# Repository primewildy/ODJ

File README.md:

# ODJ

A from-scratch DJ controller for Linux, written in Rust. Two decks, sub-3ms
output latency on PipeWire, MIDI controller support, in-app BPM + beat-grid
+ key detection, harmonic-mix filtering, and a phase vocoder for key-locked
tempo control.

Built as a side project; on the road to driving a custom microcontroller
hardware controller (RP2040 / ESP32-S3) speaking USB MIDI.

## Status

Working end-to-end as a two-deck mixing tool you can DJ a set on. Tested
with an AKAI LPD8 + homebrew **ODJ Controller** (`hardware/`) against a
library of ~550 mp3/flac tracks. The breadboard prototype of the
controller (Deck A: jog, transport buttons, 3-band EQ + volume + pitch
faders, Play LED) is fully working. A **two-deck carrier PCB**
(`hardware/pcb/`) is ready for fab — single Pico, JST-XH plug-in panel
connectors for all controls, plug-in CJMCU-4051 mux modules. A
**3D-printable faceplate** (`hardware/enclosure/`, parametric OpenSCAD)
matches it. Cue/PFL output works via a USB DAC dongle with PipeWire
routing handled automatically by `start-dj.sh`.

Built features:
- Two decks, cpal/PipeWire output at 256-frame buffers (~5.8 ms latency
  end-to-end; drops to ~2.9 ms at 128 if you run master only).
- Optional second cpal stream for **PFL / cue monitoring** on a separate
  output device (e.g. a USB DAC). **Headphone bus** with its own volume
  and a Pioneer-style **CUE↔MASTER blend** so you can mix the cued decks
  with the main mix in your headphones.
- Symphonia-based decode (mp3, flac, wav, aac/m4a).
- Phase-vocoder key-lock (with identity phase-locking for cleaner highs)
  + vinyl-style coupled-pitch mode per deck.
- 3-band EQ per deck (low 250 Hz shelf, mid 1 kHz bell, high 4 kHz shelf,
  ±25..+6 dB).
- Per-deck play-envelope (5 ms fade) — no click on transitions.
- BPM + beat-grid analysis (pure-Rust spectral flux + autocorr + brute
  force phase-aligned refinement, ~0.05 BPM precision).
- Downbeat detection via [beat_this](https://github.com/CPJKU/beat_this)
  exported to ONNX and run in-process from Rust via `ort` (CUDA EP).
  Red 4-bar lines on the beat grid; auto-snap of the playhead and cue
  point to the first downbeat on load. Optional — falls back to
  `i%4==0` if the ONNX file isn't present.
- **Live stem separation** via HTDemucs (
  [MansfieldPlumbing/Demucs_v4_TRT](https://huggingface.co/MansfieldPlumbing/Demucs_v4_TRT)
  ONNX) on the GPU through `ort` + TensorRT + FP16. ~7 s/track on an
  RTX 4060 Laptop. Three per-deck rotary knobs (DRUMS / VOCALS /
  INSTRUMENTS), 3-colour overlayed stem waveforms, in-memory
  session cache (not persisted to disk — too big). Tracks load and
  play immediately; the mixer transparently switches from the single
  buffer to the 4-stem mix when the worker finishes.
- Musical key detection (Krumhansl-Schmuckler) in Camelot notation.
- Auto Sync (BPM match) + auto Beat Align (phase-snap on play start
  *and* on every manual grid edit — so nudging a wonky grid against a
  known-good reference deck audibly converges step-by-step).
- Pioneer-style CUE state machine including the "Cue Play" commit.
- **Hot cues** — 8 slots per deck with the same set-vs-jump-vs-preview
  semantics as CUE. Jumps are beat-quantised when Q is on (defers
  the teleport to the next beat so sloppy press timing still lands
  cleanly). Right-click a slot to label it, pick a colour, or delete
  it. Persisted per-track to `.track-meta`. Coloured tick markers
  appear on both waveforms.
- **Manual beat-grid editing** — Grid Adjust tab in the source rail.
  Nudge ±1/±10 ms, skip ±1/2/4/8 beats, ½× / 2× BPM, set downbeat at
  playhead, reset. Locked by default each session so a stray click
  can't mangle a grid. Overrides persist to `.track-meta`; the manual
  grid wins over the analyser's refined output on every subsequent
  load.
- **Loops** — beat-quantised IN/OUT, one-shot 4-beat auto-loop, ½ /
  ×2 length, graceful Exit (plays out the current iteration), live
  "recording" highlight from IN to the playhead.
- **Per-deck FX** — beat-synced Echo (Type B, beat-picker UI) and
  Schroeder Reverb (Type A, continuous Time knob). Post-EQ, pre-fader
  so the cue bus tap is the wet signal.
- **Auto-mix** — armed state pre-loads a candidate next track on the
  idle deck; active blend ramps gains and drum-stem gates over the
  outgoing track's last 16 bars. Any deck-affecting user input
  cancels in-flight.
- Vinyl-style temporary push/pull nudge while held.
- Paused jog = audible scrub (forward + reverse). Click-to-seek on
  either waveform.
- Sortable track list (Title / Artist / Genre / Key / BPM / Length /
  Plays), favourites, harmonic compatibility filter, background
  analysis worker with disk persistence (and a `catch_unwind` around
  the DSP so a single pathological track can't kill the worker).
- **Session history** — every track played for ≥30 s is logged to
  `.history`. History tab groups by 2-hour gap into sessions;
  one-click setlist export to clipboard.
- **Settings UI** — audio/cue/MIDI device pickers, music-dir path,
  per-deck startup defaults. Persisted under XDG `~/.config/odj/`.
- **System theme** — light / dark follows the OS (gdbus + gsettings
  fallback); custom palette tokens for accents, stems and hot cues.
- LPD8 hardcoded mapping (pads + 8 knobs) with on-screen mirroring.
- **Homebrew hardware controller** prototype under `hardware/` — RP2040
  + optical encoder + arcade buttons + 74HC4051 analog mux. Class-
  compliant USB MIDI; sysex-triggered reboot for one-command re-flash
  (`hardware/flash.sh`). Two-deck carrier PCB (one Pico, both decks,
  JST-XH plug-in headers, CJMCU-4051 mux modules) generated from a
  SKiDL netlist (`hardware/pcb/odj_controller.py`) → KiCad → Gerbers.
  Parametric 3D-printed faceplate in `hardware/enclosure/`.

See [DESIGN.md](./DESIGN.md) for architecture and [TODO.md](./TODO.md) for
roadmap.

## Setup

Beyond `cargo` + the system audio stack, two of the bigger features need
out-of-band model files. The app runs fine without either — they're
gracefully optional — but you'll be missing red downbeat lines and stem
controls until they're in place.

All caches live under `~/.cache/dj/` (override with `$XDG_CACHE_HOME`).

### Models — runtime cache layout

| Path | What it is | Size | How to get it |
|---|---|---|---|
| `~/.cache/dj/model_final0.onnx` | beat_this downbeat model | ~85 MB | run [`scripts/export_beat_this_onnx.py`](./scripts/export_beat_this_onnx.py) in a Python venv that has `beat_this` installed, then `cp model_final0.onnx ~/.cache/dj/` |
| `~/.cache/dj/htdemucs.onnx` | HTDemucs stem-separation model | 246 MB | `curl -L -o ~/.cache/dj/htdemucs.onnx https://huggingface.co/MansfieldPlumbing/Demucs_v4_TRT/resolve/main/demucsv4.onnx` |
| `~/.cache/dj/trt-engines/` | TensorRT engine cache | ~190 MB after first build | created automatically on first stem separation (~15 min compile, cached after) |

Both files are runtime-loaded; nothing is bundled into the binary.

### TensorRT — for the fast stem path

The stems crate uses `ort`'s TensorRT execution provider. That needs
TensorRT 10.x libs (`libnvinfer.so.10`, `libnvinfer_plugin.so.10`,
`libnvonnxparser.so.10`) discoverable on `LD_LIBRARY_PATH`. The
easiest way: extract them from PyPI's `tensorrt-cu12-libs` wheel:

```sh
curl -L -o /tmp/trt.whl \
    https://pypi.nvidia.com/tensorrt-cu12-libs/tensorrt_cu12_libs-10.16.1.11-py3-none-manylinux_2_28_x86_64.whl
mkdir -p stem-spike/trt-libs && unzip -q /tmp/trt.whl -d stem-spike/trt-libs
```

`start-dj.sh` picks them up from `stem-spike/trt-libs/tensorrt_libs/`
automatically.

### CUDA — what ort needs at runtime

`ort` ships against CUDA 12 but ships a CUDA EP that's flexible.
On Arch with system CUDA 13.2 you can either:
- Install CUDA 12 alongside (e.g. via the matching `cuda-12.x` AUR
  package), or
- Use PyTorch's bundled CUDA-12 libs from a venv (set up via either
  spike script; PyTorch pulls them as `nvidia-*` packages).

`start-dj.sh` auto-prepends `stem-spike/venv/lib/python*/site-packages/nvidia/*/lib/`
to `LD_LIBRARY_PATH` if it exists, so the venv path "just works".

If neither is in place, `ort` silently falls back to CPU (stems take
~80 s/track instead of ~7 s; downbeat detection still works in
seconds).

### Music

`--music-dir music` by default (relative to CWD). Drop your library
in there; first launch pre-analyses every track in the background
(BPM, beat grid, downbeats, key) and caches results to
`<music-dir>/.analysis-cache`.

## Running

The convenient way (handles PipeWire routing for the cue stream and
restores your normal audio setup on exit):

```
./start-dj.sh
```

That's a thin wrapper around `cargo run --release` with sensible flags
and some PipeWire choreography (see [`docs/notes/pipewire_routing.md`](docs/notes/pipewire_routing.md)).
Or run the binary directly:

```
cargo run --release -- [--device <cpal-name>] [--cue-device <cpal-name>] \
                      [--midi <port-substring>] [--music-dir <path>]
```

Defaults / behaviour:
- `--device` unset → uses the cpal `pipewire` device for the master out.
  Override to target a specific sink directly. When the cpal device name
  is `pipewire`, the `PIPEWIRE_NODE` env var (if set) is honoured.
- `--cue-device` unset → no cue stream is opened; deck `cue` toggles
  have no audible effect. Set this to a cpal device name to enable PFL
  monitoring. If cpal can't find that name in its ALSA enumeration
  (common for USB DACs on PipeWire systems), it falls back to looking up
  a PipeWire sink whose name contains the same substring and routes the
  cue stream to it via `PIPEWIRE_NODE` — so e.g. `--cue-device "KT USB"`
  finds `alsa_output.usb-…KT_USB_Audio…` without needing the full name.
  The two streams have independent clocks; drift is irrelevant for cue
  since master and cue are heard on separate transducers.
- `--midi "ODJ"` is what `start-dj.sh` passes; matches the homebrew
  controller's USB-MIDI port name. The binary's default is `"LPD8"` for
  legacy dev with an AKAI pad; either substring works. Set to `""` to
  disable MIDI entirely.
- `--music-dir music` (relative to CWD). Audio files in this directory
  (non-recursive) populate the in-app track list.

Per-build controller quirks (e.g. a backward-wired fader) go in
`controls.toml` in the working directory — see `controls.toml.example`.
It's read at startup; currently supports `invert_cc = [...]` to flip
specific MIDI CCs. Gitignored since it's hardware-specific.

The first launch with a populated music directory will spend a few minutes
in the background pre-analysing every track (BPM + beat grid + key).
Progress shows in the top bar. Cache file `<music-dir>/.analysis-cache`
makes subsequent launches instant.

## Controls

### Keyboard
- `space` Deck A play/pause toggle
- `c` (hold) Deck A CUE (Pioneer state machine; press while paused at cue
  starts preview, release returns to cue)
- `b` Deck B play/pause toggle
- `n` (hold) Deck B CUE

### LPD8 (factory PROG-1 defaults)

Layout — top row pads/knobs = Deck A, bottom row = Deck B:

```
[K1 K2 K3 K4]    [Pad 5 Pad 6 Pad 7 Pad 8]    ← Deck A
[K5 K6 K7 K8]    [Pad 1 Pad 2 Pad 3 Pad 4]    ← Deck B
```

| Pad | Deck | Function                                    |
|-----|------|---------------------------------------------|
| 5   | A    | Play / pause toggle                         |
| 6   | A    | CUE (Pioneer state machine, hold for preview)|
| 7   | A    | Pull (slower while held — vinyl push/pull)  |
| 8   | A    | Push (faster while held)                    |
| 1   | B    | Play / pause toggle                         |
| 2   | B    | CUE                                         |
| 3   | B    | Pull                                        |
| 4   | B    | Push                                        |

| Knob | Deck | Function                                       |
|------|------|------------------------------------------------|
| K1   | A    | Pitch (CC 64 = unity, ±8% range)              |
| K2   | A    | Volume (linear 0..1)                           |
| K3   | A    | EQ high (CC 64 = flat, ±25..+6 dB)            |
| K4   | A    | EQ low                                         |
| K5   | B    | Pitch                                          |
| K6   | B    | Volume                                         |
| K7   | B    | EQ high                                        |
| K8   | B    | EQ low                                         |

If your LPD8 sends different note/CC numbers, every incoming MIDI message
is logged to stderr — read them off and edit the `match` arms in
`src/midi.rs`.

## Project layout

```
/
├── Cargo.toml          # workspace + binary
├── start-dj.sh         # launch wrapper — PipeWire routing for the cue
│                       #   stream, auto-restores your normal setup
├── src/
│   ├── main.rs         # eframe entry, CLI parse, MIDI thread spawn
│   └── midi.rs         # LPD8 / ODJ Controller MIDI input + jog handler
├── crates/
│   ├── control/        # DeckCommand enum, MusicalKey, ring buffer types
│   ├── decode/         # symphonia → TrackBuffer
│   ├── analysis/       # BPM + beat grid + downbeats (ONNX) + key
│   ├── stems/          # HTDemucs ONNX wrapper
│   ├── audio/          # cpal stream(s), mixer, EQ, FX, phase vocoder
│   └── ui/             # eframe app — see crate-level breakdown in
│                       #   DESIGN.md §4 (auto_mix, grid_edit, history,
│                       #   palette, persistence, settings, theme, fonts)
└── hardware/
    ├── firmware/       # Pico SDK C project (breadboard Deck A)
    ├── pcb/            # two-deck carrier — SKiDL netlist + KiCad
    │   ├── odj_controller.py   # SKiDL → odj_controller.net
    │   └── odj.pretty/         # project-local footprints (Pico,
    │                           #   CJMCU-4051 mux module)
    ├── enclosure/      # 3D-printable faceplate — parametric OpenSCAD
    ├── SCHEMATIC.md    # Deck-A breadboard wiring reference
    └── flash.sh        # sysex-reboot auto-flash workflow
```

## Acknowledgements

Beat-detection pipeline drew on the standard MIR cookbook (spectral flux
+ autocorrelation, with phase-aligned brute-force refinement). Key
detection uses the Krumhansl-Kessler profiles. Pioneer CDJ CUE behaviour
was researched against the CDJ-3000 / CDJ-2000NXS instruction manuals.

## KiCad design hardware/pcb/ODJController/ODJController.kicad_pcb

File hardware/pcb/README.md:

# ODJ controller PCB (two-deck carrier board)

A single-board carrier that drives **both decks** from one Raspberry Pi Pico.
Everything off-board (pots, faders, buttons, encoders, LEDs) lands on **JST-XH**
connectors — locking and polarised, so panel cables can't be plugged in
backwards. Bench/expansion points (spare GPIO, I2C) use 2.54 mm pin headers for
jumper wires and plug-in modules. The Pico and the two **CJMCU-4051 mux
modules** all socket onto headers — nothing solders to the PCB except the
connectors and the decoupling parts.

The board is described in code (`odj_controller.py`, using
[SKiDL](https://github.com/devbisme/skidl)) and the KiCad netlist is generated
from it. The script is the source of truth; the `.net` file is a build
artifact (regenerate it, don't hand-edit).

```
USB ── Pico ─┬─ Deck A: jog encoder, 4 buttons, Play+🎧Cue LEDs, mux A (GP26/ADC0)
             └─ Deck B: jog encoder, 4 buttons, Play+🎧Cue LEDs, mux B (GP27/ADC1)
             shared mux select S0/S1/S2 (GP6/7/8)
```

Why one Pico for two decks: the host (`src/midi.rs`) already maps both decks
from a single MIDI stream, and the RP2040 has the I/O (≈21 of 26 usable GPIO).
One USB cable, one firmware, no inter-board sync.

## Generate the netlist

SKiDL is a Python package; KiCad need not be installed to *generate* the
netlist (the parts carry explicit pin definitions). You only need KiCad for the
layout step.

```
python3 -m venv venv
. venv/bin/activate
pip install skidl
python odj_controller.py        # writes odj_controller.net
```

## Lay out + route in KiCad → Gerbers

The schematic capture is done (it's the netlist). The remaining work — placing
parts and routing copper — is the visual part KiCad is for. A 2-layer board is
plenty.

1. Install **KiCad (10.x)** *and its library package* — the footprints and
   symbols are a separate ~370 MB package. On Arch this bites everyone:

   ```
   sudo pacman -S kicad kicad-library kicad-library-3d
   ```

   Installing `kicad` alone leaves `/usr/share/kicad/{symbols,footprints}`
   empty and every library "missing". KiCad provides sane defaults for the
   `KICAD10_FOOTPRINT_DIR` / `KICAD10_SYMBOL_DIR` path variables internally;
   if a stale `~/.config/kicad` from an older version points them wrong, check
   **Preferences → Configure Paths…** (they should be `/usr/share/kicad/...`).
   Then open the **PCB editor** (skip Eeschema; we import the netlist straight
   into the board).
2. **Register this repo's footprint library.** KiCad ships no Pico or
   4051-module footprint, so clean ones live at `hardware/pcb/odj.pretty/`. In
   the PCB editor: **Preferences → Manage Footprint Libraries → Project Specific
   Libraries** (or Global) → add the path `…/hardware/pcb/odj.pretty` with
   nickname **`odj`**. Now `odj:RPi_Pico_THT` and `odj:CJMCU_4051` resolve.
3. **File → Import → Netlist…** → pick `odj_controller.net` → set *Link Method*
   to **reference designators** (SKiDL randomises the unique-id tstamps each
   regeneration, so refdes is the stable choice for re-imports) → *Update PCB*.
   Footprints land in a heap with a ratsnest showing every connection. Every
   footprint resolves: the stock KiCad parts plus the Pico (`odj:RPi_Pico_THT`,
   a single 40-pad part — no hand-aligning two halves).
   - **The Pico** is one footprint with both 1×20 rows already 17.78 mm (0.7")
     apart; solder two 1×20 female sockets into it and the Pico plugs in.
4. Draw the board outline, place parts (see layout tips below), route, add
   ground pours on both layers, run **DRC**.
5. **File → Plot** Gerbers + **Generate Drill Files**, zip them, upload to
   JLCPCB / PCBWay / OSHPark. ~£5 for 5 boards from JLCPCB.

## Layout tips that matter

- **Decoupling close.** Put a 100 nF on the 3V3 rail near each mux module's VCC
  pin (the modules self-bypass too), and one at the Pico's 3V3↔GND. The 10 µF
  bulk near the 3V3 entry.
- **Don't filter the ADC line.** No cap on `MUXA_Z`/`MUXB_Z` — the firmware
  settles the mux in 5 µs, and a cap + the pot's ~10 kΩ source would smear one
  channel's reading into the next. Keep these two traces short instead, and
  away from the USB and encoder lines.
- **Star the analog ground** back to a Pico GND pin (33/38) if you can; keeps
  pot noise out of the ADC.
- Encoders are NPN open-collector → no level shifter; the 4-pin header carries
  +5V (VBUS), A, B, GND.

## Bill of materials

| Qty | Part | Notes |
|-----|------|-------|
| 1 | Raspberry Pi Pico | with male pin headers soldered on |
| 2 | 1×20 female socket header | sockets the Pico (rows 0.7"/17.78 mm apart) |
| 2 | CJMCU-4051 74HC4051 mux module | already owned (30×19 mm). Socket each with an 8-way + 11-way female header strip, or solder it in. VCC → 3V3 (it's HC, not HCT). |
| 2 | Rotary encoder, 600 P/R, NPN open-collector | jog wheels |
| 8 | Illuminated arcade button, 24 mm | Play/Cue/🎧Cue/Sync × 2 decks |
| 4 | Slide fader (10 kΩ) | pitch + volume × 2 decks |
| 6 | Rotary pot B10K | 3-band EQ × 2 decks |
| 3 | Ceramic cap 100 nF | mux ×2 + Pico decoupling |
| 1 | Electrolytic cap 10 µF | 3V3 bulk |
| 4 | Resistor | 0 Ω link (arcade LED has its own R) or ~150 Ω for a bare LED |
| 16 | JST-XH 1×3 (B3B-XH-A) | analog channels (8 per mux) |
| 12 | JST-XH 1×2 (B2B-XH-A) | 8 buttons + 4 LEDs (Play + 🎧Cue × 2 decks) |
| 2 | JST-XH 1×4 (B4B-XH-A) | jog encoders |
| 1 | 1×4 pin header | I2C expansion |
| 1 | 1×10 pin header | spare-GPIO breakout |

Plus the JST-XH cable side: matching 2/3/4-way housings + crimp contacts (or
pre-crimped leads) to wire each panel control back to its board connector —
16× 3-way, 12× 2-way, 2× 4-way.

## Pin map (mirrors `hardware/firmware/src/main.c`)

Keep this and the firmware in sync.

| Signal | GPIO | Pico pin | Connects to |
|--------|------|----------|-------------|
| Mux select S0 | GP6 | 9 | both muxes pin 11 |
| Mux select S1 | GP7 | 10 | both muxes pin 10 |
| Mux select S2 | GP8 | 11 | both muxes pin 9 |
| Mux A common Z | GP26/ADC0 | 31 | mux A pin 3 — Deck A analog |
| Mux B common Z | GP27/ADC1 | 32 | mux B pin 3 — Deck B analog |
| Deck A jog A / B | GP14 / GP15 | 19 / 20 | A-ENCODER header |
| Deck B jog A / B | GP16 / GP17 | 21 / 22 | B-ENCODER header |
| Deck A Play btn | GP10 | 14 | A-PLAY (note 40) |
| Deck A Cue btn | GP11 | 15 | A-CUE (note 41) |
| Deck A 🎧Cue btn | GP12 | 16 | A-HPCUE (note 44) |
| Deck B Play btn | GP13 | 17 | B-PLAY (note 36) |
| Deck B Cue btn | GP19 | 25 | B-CUE (note 37) |
| Deck B 🎧Cue btn | GP20 | 26 | B-HPCUE (note 45) |
| Deck A Sync btn | GP2 | 4 | A-SYNC (note 46) |
| Deck B Sync btn | GP3 | 5 | B-SYNC (note 47) |
| Deck A Play LED | GP18 | 24 | A_PLAY-LED via R1 (host note 40) |
| Deck A 🎧Cue LED (PFL) | GP22 | 29 | A_HPCUE-LED via R2 (host note 44) |
| Deck B Play LED | GP21 | 27 | B_PLAY-LED via R3 (host note 36) |
| Deck B 🎧Cue LED (PFL) | GP9 | 12 | B_HPCUE-LED via R4 (host note 45) |

The 🎧Cue LED is a **PFL indicator** — lit while that deck is routed to the
headphones, not tied to the transport-cue point. The transport-Cue button
(notes 41 / 37) has no Pico-driven LED.

Both muxes use the same channel layout (channel = `S2 S1 S0`):

| Ch | Y-pin | Function | Deck A CC | Deck B CC |
|----|-------|----------|-----------|-----------|
| 0 | Y0 (13) | EQ low | 4 | 8 |
| 1 | Y1 (14) | EQ mid | 9 | *(new)* |
| 2 | Y2 (15) | EQ high | 3 | 7 |
| 3 | Y3 (12) | Volume | 2 | 6 |
| 4 | Y4 (1) | Pitch | 1 | 5 |
| 5–7 | Y5/Y6/Y7 | spare (broken out) | — | — |

## Expansion (extra button banks: effects, hot cues)

Two independent routes — they coexist, use either or both:

**A. Standalone USB-MIDI pad controllers.** A cheap 16-pad USB controller just
plugs into the laptop as its own MIDI device — nothing touches this PCB. This
is a *host* change, not a hardware one: `src/midi.rs` currently connects to a
single MIDI input port; supporting extra controllers means opening multiple
ports and mapping the pad notes to hot-cue / FX commands. The engine is already
ready for it — `Sender` is cloneable, so any MIDI producer can drive a deck.

**B. Raw buttons wired to this board.** For tightly-integrated pads, the board
is built to grow without a respin:

- **I2C-EXP header** taps I2C0 (GP0=SDA, GP1=SCL) + 3V3 + GND. Hang an
  **MCP23017-style I/O expander** off it: 16 buttons per chip on two wires,
  chain up to 8 (128 buttons). Firmware polls it over I2C.
- **Spare-GPIO header** breaks out GP0–GP5, GP9, GP22, GP28 (ADC2) + power —
  enough for a **4×4 matrix scan** (16 buttons on 8 GPIO) for one cluster.

Either way the new pads emit MIDI the host maps to hot-cue / FX commands — no
change to this PCB.

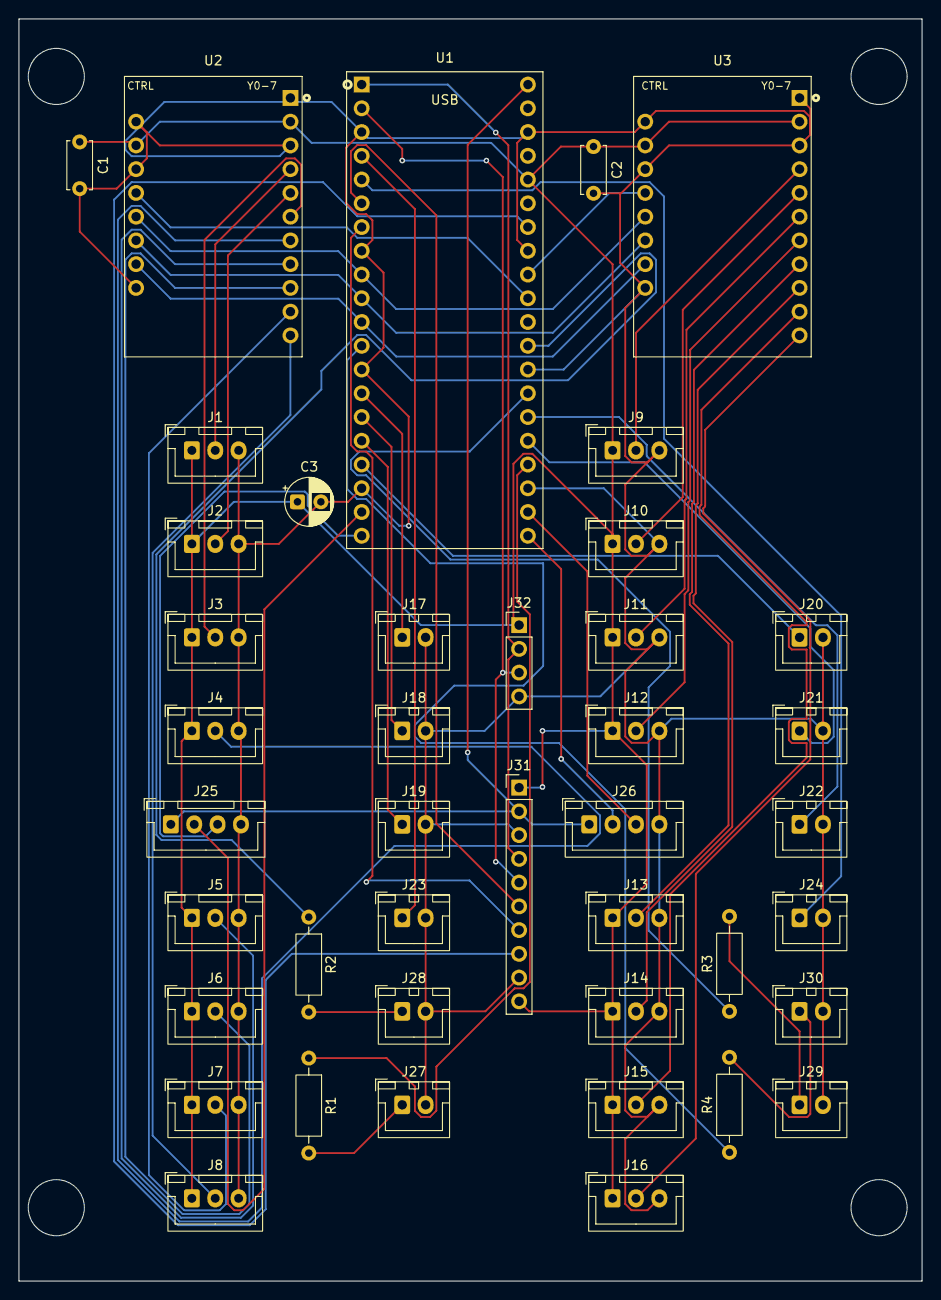
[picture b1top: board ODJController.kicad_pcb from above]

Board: 2 copper layers, 96.6 x 135.0 mm, 42 parts (0 on the bottom side), 49 nets.

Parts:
C1, C2: 100nF; C_Disc_D5.0mm_W2.5mm_P5.00mm
C3: 10uF; CP_Radial_D5.0mm_P2.50mm
J1: A-EQ_LOW; JST_XH_B3B-XH-A_1x03_P2.50mm_Vertical
J2: A-EQ_MID; JST_XH_B3B-XH-A_1x03_P2.50mm_Vertical
J3: A-EQ_HIGH; JST_XH_B3B-XH-A_1x03_P2.50mm_Vertical
J4: A-VOLUME; JST_XH_B3B-XH-A_1x03_P2.50mm_Vertical
J5: A-PITCH; JST_XH_B3B-XH-A_1x03_P2.50mm_Vertical
J6: A-SPARE5; JST_XH_B3B-XH-A_1x03_P2.50mm_Vertical
J7: A-SPARE6; JST_XH_B3B-XH-A_1x03_P2.50mm_Vertical
J8: A-SPARE7; JST_XH_B3B-XH-A_1x03_P2.50mm_Vertical
J9: B-EQ_LOW; JST_XH_B3B-XH-A_1x03_P2.50mm_Vertical
J10: B-EQ_MID; JST_XH_B3B-XH-A_1x03_P2.50mm_Vertical
J11: B-EQ_HIGH; JST_XH_B3B-XH-A_1x03_P2.50mm_Vertical
J12: B-VOLUME; JST_XH_B3B-XH-A_1x03_P2.50mm_Vertical
J13: B-PITCH; JST_XH_B3B-XH-A_1x03_P2.50mm_Vertical
J14: B-SPARE5; JST_XH_B3B-XH-A_1x03_P2.50mm_Vertical
J15: B-SPARE6; JST_XH_B3B-XH-A_1x03_P2.50mm_Vertical
J16: B-SPARE7; JST_XH_B3B-XH-A_1x03_P2.50mm_Vertical
J17: A-PLAY; JST_XH_B2B-XH-A_1x02_P2.50mm_Vertical
J18: A-CUE; JST_XH_B2B-XH-A_1x02_P2.50mm_Vertical
J19: A-HPCUE; JST_XH_B2B-XH-A_1x02_P2.50mm_Vertical
J20: B-PLAY; JST_XH_B2B-XH-A_1x02_P2.50mm_Vertical
J21: B-CUE; JST_XH_B2B-XH-A_1x02_P2.50mm_Vertical
J22: B-HPCUE; JST_XH_B2B-XH-A_1x02_P2.50mm_Vertical
J23: A-SYNC; JST_XH_B2B-XH-A_1x02_P2.50mm_Vertical
J24: B-SYNC; JST_XH_B2B-XH-A_1x02_P2.50mm_Vertical
J25: A-ENCODER; JST_XH_B4B-XH-A_1x04_P2.50mm_Vertical
J26: B-ENCODER; JST_XH_B4B-XH-A_1x04_P2.50mm_Vertical
J27: A_PLAY-LED; JST_XH_B2B-XH-A_1x02_P2.50mm_Vertical
J28: A_HPCUE-LED; JST_XH_B2B-XH-A_1x02_P2.50mm_Vertical
J29: B_PLAY-LED; JST_XH_B2B-XH-A_1x02_P2.50mm_Vertical
J30: B_HPCUE-LED; JST_XH_B2B-XH-A_1x02_P2.50mm_Vertical
J31: SPARE-GPIO; PinHeader_1x10_P2.54mm_Vertical
J32: I2C-EXP; PinHeader_1x04_P2.54mm_Vertical
R1, R2, R3, R4: 0R; R_Axial_DIN0207_L6.3mm_D2.5mm_P10.16mm_Horizontal
U1: RPi_Pico; RPi_Pico_THT
U2, U3: CJMCU_4051

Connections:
+3V3: C1.1, C2.1, C3.1, J1.1, J2.1, J3.1, J4.1, J5.1, J6.1, J7.1, J8.1, J9.1, J10.1, J11.1, J12.1, J13.1, J14.1, J15.1, J16.1, J31.1, J31.10, J32.1, U1.36, U2.2, U2.13, U3.2, U3.13
+5V: J25.1, J26.1, J31.2, U1.40
AN_A0_EQ_LOW: J1.2, U2.4
AN_A1_EQ_MID: J2.2, U2.5
AN_A2_EQ_HIGH: J3.2, U2.6
AN_A3_VOLUME: J4.2, U2.7
AN_A4_PITCH: J5.2, U2.8
AN_A5_SPARE5: J6.2, U2.9
AN_A6_SPARE6: J7.2, U2.10
AN_A7_SPARE7: J8.2, U2.11
AN_B0_EQ_LOW: J9.2, U3.4
AN_B1_EQ_MID: J10.2, U3.5
AN_B2_EQ_HIGH: J11.2, U3.6
AN_B3_VOLUME: J12.2, U3.7
AN_B4_PITCH: J13.2, U3.8
AN_B5_SPARE5: J14.2, U3.9
AN_B6_SPARE6: J15.2, U3.10
AN_B7_SPARE7: J16.2, U3.11
BTN_A_CUE: J18.1, U1.15
BTN_A_HPCUE: J19.1, U1.16
BTN_A_PLAY: J17.1, U1.14
BTN_A_SYNC: J23.1, U1.4
BTN_B_CUE: J21.1, U1.25
BTN_B_HPCUE: J22.1, U1.26
BTN_B_PLAY: J20.1, U1.17
BTN_B_SYNC: J24.1, U1.5
ENCA_A: J25.2, U1.19
ENCA_B: J25.3, U1.20
ENCB_A: J26.2, U1.21
ENCB_B: J26.3, U1.22
GND: C1.2, C2.2, C3.2, J1.3, J2.3, J3.3, J4.3, J5.3, J6.3, J7.3, J8.3, J9.3, J10.3, J11.3, J12.3, J13.3, J14.3, J15.3, J16.3, J17.2, J18.2, J19.2, J20.2, J21.2, J22.2, J23.2, J24.2, J25.4, J26.4, J27.2, J28.2, J29.2, J30.2, J31.3, J31.9, J32.4, U1.3, U1.8, U1.13, U1.18, U1.23, U1.28, U1.33, U1.38, U2.1, U2.3, U2.12, U2.14, U2.19, U3.1, U3.3, U3.12, U3.14, U3.19
LED_A_HPCUE: J28.1, R2.2
LED_A_HPCUE_GP: R2.1, U1.29
LED_A_PLAY: J27.1, R1.2
LED_A_PLAY_GP: R1.1, U1.24
LED_B_HPCUE: J30.1, R4.2
LED_B_HPCUE_GP: R4.1, U1.12
LED_B_PLAY: J29.1, R3.2
LED_B_PLAY_GP: R3.1, U1.27
MUXA_Z: U1.31, U2.15
MUXB_Z: U1.32, U3.15
MUX_S0: U1.9, U2.16, U3.16
MUX_S1: U1.10, U2.17, U3.17
MUX_S2: U1.11, U2.18, U3.18
SP_GP0: J31.4, J32.2, U1.1
SP_GP1: J31.5, J32.3, U1.2
SP_GP4: J31.6, U1.6
SP_GP5: J31.7, U1.7
SP_GP28: J31.8, U1.34

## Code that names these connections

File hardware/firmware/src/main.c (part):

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#define PIN_ENC_B_B    17  // Deck B encoder B phase

// Buttons — 8 total, 4 per deck (PLAY, CUE, 🎧-CUE/HPCUE, SYNC).
#define PIN_BTN_A_PLAY   10  // note 40
#define PIN_BTN_A_CUE    11  // note 41
#define PIN_BTN_A_HPCUE  12  // note 44
#define PIN_BTN_A_SYNC    2  // note 46
#define PIN_BTN_B_PLAY   13  // note 36
#define PIN_BTN_B_CUE    19  // note 37
#define PIN_BTN_B_HPCUE  20  // note 45
#define PIN_BTN_B_SYNC    3  // note 47

// Mux — shared select lines, separate output pins on different ADC channels.
#define PIN_MUX_S0        6
#define PIN_MUX_S1        7
#define PIN_MUX_S2        8
#define PIN_MUX_A_OUT    26  // GP26 / ADC0 — Deck A mux
#define PIN_MUX_B_OUT    27  // GP27 / ADC1 — Deck B mux
#define ADC_INPUT_A       0
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//   note 36 → Deck B PLAY
//   note 44 → Deck A 🎧-CUE     (lit while Deck A is on the cue bus)
//   note 45 → Deck B 🎧-CUE
#define PIN_LED_A_PLAY    18
#define PIN_LED_A_HPCUE   22
#define PIN_LED_B_PLAY    21
#define PIN_LED_B_HPCUE    9

// ===== MIDI mapping =====

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
#define NUM_BUTTONS 8
static const uint8_t BUTTON_PIN[NUM_BUTTONS] = {
    PIN_BTN_A_PLAY, PIN_BTN_A_CUE, PIN_BTN_A_HPCUE, PIN_BTN_A_SYNC,
    PIN_BTN_B_PLAY, PIN_BTN_B_CUE, PIN_BTN_B_HPCUE, PIN_BTN_B_SYNC,
};
static const uint8_t BUTTON_NOTE[NUM_BUTTONS] = {
    40, 41, 44, 46,   // Deck A: PLAY, CUE, HPCUE, SYNC
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// ===== Multiplexer + ADC =====

static inline void mux_select(uint8_t channel) {
    gpio_put(PIN_MUX_S0, (channel >> 0) & 1u);
    gpio_put(PIN_MUX_S1, (channel >> 1) & 1u);
    gpio_put(PIN_MUX_S2, (channel >> 2) & 1u);
}

// Set to 1 to stream every mux channel every scan, ignoring the
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static void handle_note(uint8_t note, bool on) {
    // Mirror host's deck-state notes back onto button LEDs.
    switch (note) {
        case 40: gpio_put(PIN_LED_A_PLAY,  on); break;  // Deck A playing
        case 44: gpio_put(PIN_LED_A_HPCUE, on); break;  // Deck A 🎧-cue active
        case 36: gpio_put(PIN_LED_B_PLAY,  on); break;  // Deck B playing
        case 45: gpio_put(PIN_LED_B_HPCUE, on); break;  // Deck B 🎧-cue active
        default: break;
    }
}
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    PIN_ENC_A_A, PIN_ENC_A_B, PIN_ENC_B_A, PIN_ENC_B_B,
};
static const uint8_t LED_PINS[4] = {
    PIN_LED_A_PLAY, PIN_LED_A_HPCUE, PIN_LED_B_PLAY, PIN_LED_B_HPCUE,
};

static void init_gpio(void) {
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        button_debounce_until[i] = boot_zero;
    }

    gpio_init(PIN_MUX_S0); gpio_set_dir(PIN_MUX_S0, GPIO_OUT); gpio_put(PIN_MUX_S0, 0);
    gpio_init(PIN_MUX_S1); gpio_set_dir(PIN_MUX_S1, GPIO_OUT); gpio_put(PIN_MUX_S1, 0);
    gpio_init(PIN_MUX_S2); gpio_set_dir(PIN_MUX_S2, GPIO_OUT); gpio_put(PIN_MUX_S2, 0);

    for (int i = 0; i < 4; i++) {
        gpio_init(LED_PINS[i]);
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
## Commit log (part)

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2026-05-31 ui: rotary knobs for EQ + vertical pitch/vol faders + track list height
    Three small UI fixes:
    - EQ controls are now Pioneer-style rotary knobs (HIGH / MID / LOW),
    click-and-drag vertically to change value, double-click to reset to
    0 dB. Replaces the horizontal sliders that didn't fit the mixer
    channel-strip layout.
    - PITCH and VOL become vertical faders side-by-side, matching real DJ
2026-05-31 docs(downbeat): capture spike findings — beat_this + ONNX + custom postproc
    A 2026-05-31 spike to decide how to fix the "beat 4 vs beat 1"
    problem (Moonlight by Mandragora/Beltran is the smoking gun). The
    current analysis pipeline finds the beat period but doesn't have any
    notion of bar phase — `i % 4 == 0` in the UI is luck-of-the-draw.
    The spike validates:
    - beat_this (Foroughmand et al. 2024, MIT) loads + runs on Python 3.14;
2026-05-31 ui: channel-strip layout + preserve play state on track load
    Three QoL fixes that pile up nicely:
    - EQ knobs (HIGH / MID / LOW) now sit ABOVE the volume fader, the way
    a real DJ-mixer channel strip is laid out. Pitch fader stays on the
    left as a "deck" control.
    - Header title now truncates with an ellipsis instead of wrapping, so
    loading a track with a long name doesn't push the controls around.
2026-05-31 analysis: scaffold beat_this ONNX inference via tract
    Adds the foundation for the downbeat detection v1.5 work:
    - `crates/analysis::downbeat` module — loads the beat_this ONNX
    checkpoint via tract-onnx (pure Rust, no native libonnxruntime
    download) and exposes `infer_chunk()` running a single
    (1, 1500, 128) input through the compiled graph.
    - Model lives at `$XDG_CACHE_HOME/dj/model_final0.onnx` (~85 MB);
2026-05-31 ui: lock deck column widths + centre vol under EQ knobs
    Two fixes:
    - Each deck column's inner UI is now strictly clipped to its half of
    the central panel (ui.set_min_width + set_max_width inside the
    allocate_ui_with_layout closure). A long track title on Deck A can
    no longer push Deck B around — the midline is fixed unless the
    window itself is resized.
2026-05-31 analysis: beat_this downbeats via mid-track window + 4/4 back-projection
    Phase 2 of the ML port — the model now actually drives the downbeat
    column shown on the waveform.
    Key pieces:
    - **logmel.rs**: Slaney-mel + periodic Hann + frame_length norm +
    log1p(1000·mel) + center=True reflection padding. Tested per-element
    against a torchaudio dump from beat_this' own LogMelSpect (max_abs
2026-05-31 ux: snap playhead to first downbeat + red lines every 4 bars
    Two small renderer / mixer tweaks once downbeats are available:
    - LoadTrack handler now sets `deck.playhead` and `deck.cue_frame` to
    the first downbeat from the analysis (in samples) instead of t=0.
    Most tracks have a second or two of room tone / pickup before the
    first kick lands; we skip it automatically so Play and CUE both
    behave the way a DJ expects. Falls back to t=0 if no downbeats are
2026-05-31 ui: async track load — play immediately, refine beat grid in background
    Loading an uncached track no longer blocks on analysis. The flow is
    now two-phase:
    1. **Fast path** — decode + waveform compute (~1 s for a 5-min track),
    then send `LoadTrack` to the audio engine with whatever's already in
    the cache (or an empty TrackAnalysis when there's nothing). The
    deck becomes playable straight away. UI receives a `LoadEvent::Initial`
2026-05-31 analysis: half-bar override when beat[0] is a strong kick
    beat_this gets the bar phase wrong on some dance tracks — confidently
    half-a-bar off, mistaking kicks-on-2-and-4 for kicks-on-1-and-3.
    Confirmed on four tracks today (Are We Truly Free, two Emotion edits,
    Don't Touch That Dial all had the wrong "1" pre-fix).
    The pattern: for dance music, beat[0] is almost always the real "1"
    — a strong, isolated kick at the very start of the audio. Tracks
2026-05-31 analysis: phrase-boundary cross-check + continuous repaint
    Two unrelated changes that needed shipping together because they
    touch related plumbing:
    - **Phrase boundaries vote on bar phase.** Detects breaks (smoothed
    spectral-flux envelope drops to <25 % of the active-section mean
    for >=2 s) and re-entries (climbs back above 60 %). The DSP beat
    closest to each re-entry is by construction a bar-1 downbeat, so
2026-05-31 analysis: detect phantom beats in silent intros
    The DSP autocorr picks a constant tempo + a single global phase and
    generates the beat grid by stepping forward from that phase. When the
    phase lands in the silent intro (e.g. Don't Touch That Dial: the
    first audible beat is at ~1 s but the period propagates backwards to
    plant beats at 0.085 s and 0.539 s), the FIRST audible beat ends up
    at `beat[2]`, not `beat[0]`.
2026-05-31 analysis + audio: log track names, drop phrase-boundary check, ease audio underruns
    A grab-bag fixing today's observations from the running app.
    - **Track names in the analysis log.** Worker now prints
    `analysing: <filename>` before each track, so the half-bar /
    silent-leading-beats / phrase-boundary log lines have a clear
    parent. (User asked for this directly when scanning the worker's
    output.)
2026-05-31 start-dj.sh: set LD_LIBRARY_PATH so the binary finds libonnxruntime
    The copy-dylibs feature symlinks libonnxruntime.so + the CUDA EP
    libs into target/release/. Cargo sets the loader path automatically
    when invoking the binary, but our script now execs it directly
    (switched in the previous commit to avoid the 10 s stream-discovery
    poll racing the rebuild). Without the path set we get:
    target/release/dj: error while loading shared libraries:
2026-05-31 analysis: regression test for The Way I Like It
    Confirms the algorithm picks beat[0] as the first downbeat on a
    track with a soft (non-kick) start. The model wants offset 3 but
    the half-bar override fires because beat[0]'s env is well into the
    top-30 % (489 vs mean of 99); silent-leading-beats also does not
    fire (env far above the 10 % threshold). Same path that fixed
    Are We Truly Free and the Emotion family.
2026-05-31 stems: control plumbing + UI knobs (no inference yet)
    First slice of the stem-mixing work — gets the control surface and
    audio engine wired through end-to-end with placeholder data, so the
    UI can be eyeballed before the inference backend lands.
    What's in:
    - `TrackStems` (drums / bass / vocals / other interleaved buffers)
    in the control crate, shared via Arc the same way TrackBuffer is.
2026-05-31 stems: HTDemucs separation + session cache + live mixer path
    Iterations 2 + 3 of the stem work, end-to-end audible result.
    **Separation backend (iteration 2).** New `stems` crate. Per-process
    SessionCache backed by a tempdir under \$TMPDIR/dj-stems-<pid>/
    (cleaned up on Drop). `separate(path)` either returns a cached
    Arc<TrackStems> or shells out to `python -m demucs.separate
    --device cuda` in the spike's venv. ~15 s/track on the RTX 4060
2026-05-31 stems: route SetStems through the UI drain to dodge the cross-track race
    If the user loaded a second track while the first track's demucs job
    was still running, the stem worker's `DeckCommand::SetStems` would
    land on the engine after `DeckCommand::LoadTrack` for the new track
    — and the mixer would happily start mixing track A's stems against
    track B's buffer (sample-rate / frame-count happen to match for most
    files, so the existing geometry guard wouldn't catch it).
2026-05-31 stems: stderr diagnostics for the SetStems path
    User reports knobs don't do anything after demucs completes — log
    both ends of the LoadEvent::Stems → SetStems pipeline to figure out
    where it's silently dropping:
    - UI drain prints either "applied" (with frames/sr/ch) or "drop
    (deck moved on)" with the path mismatch.
    - Engine SetStems handler prints buffer vs stems geometry and
2026-05-31 stems: rename to DRUMS / VOCALS / INSTR + relax buffer-match check + UI status
    User feedback addressed:
    1. Stem labels renamed (and the routing was wrong before, sed did
    the variable rename but the actual mixing formula still summed
    vocals + other for "melody"). New routing:
    - DRUMS knob → drums stem only
    - VOCALS knob → vocals stem only (clean isolation for mashups)
2026-05-31 audio: diagnostic match reflects the actual relaxed guard
    The eprintln on SetStems was using the old strict
    `stems.frames() >= buf.frames()` check, so it printed false even
    though the real render-path guard now allows ~1 s slack
    (demucs's chunk boundaries make ±a few hundred sample mismatches
    normal). Now logs 'will use? true/false' from the same expression
    the renderer evaluates.
2026-05-31 docs(stems): record failed HTDemucs ONNX export attempt + decision
    Spent a session on the 'stems-onnx-export' feature branch trying to
    drop the Python demucs subprocess. Two distinct failure modes:
    1. Torchscript exporter: aten::stft can't translate complex types
    ("STFT does not currently support complex types"). Replacing
    spectro/ispectro with conv-based real-valued equivalents
    requires patching 4-6 downstream call sites in htdemucs.py
2026-05-31 docs: HTDemucs ONNX export now working
    Updated note to reflect the export succeeding (after four targeted
    monkey-patches in the spike script). max abs diff vs PyTorch is
    7e-05 on a real audio clip — numerically identical within FP32
    rounding noise.
    Inlined model is 171 MB. Next: move it to ~/.cache/dj/ and port
    the stems crate from the Python subprocess to ort + ONNX inference,
2026-05-31 start-dj.sh: point ort's CUDA EP at PyTorch's bundled CUDA-12 libs
    pyke's libonnxruntime_providers_cuda.so is built against CUDA 12 but
    the system has CUDA 13.2 — \`libcublas.so.12\` / \`libcudart.so.12\`
    etc. don't exist, so ort silently falls back to CPU and stems take
    ~80 s per 5-min track instead of the ~10 s the GPU can manage.
    PyTorch's pip install in stem-spike/venv bundles its own CUDA-12
    runtime libs as nvidia-* packages. Prepend those lib dirs to
2026-06-01 stems: overlap-add at chunk boundaries (matches demucs's apply_model)
    User reported separation quality worse than Python demucs. Cause:
    hard cuts between 7.8 s chunks were producing audible artefacts at
    every chunk boundary (clicks / mid-phrase splits).
    Fix: process chunks with OVERLAP samples (0.5 s) of overlap on each
    side and stride = MODEL_CHUNK - 2*OVERLAP. Each chunk's output is
    multiplied by a triangular window (ramp-up over OVERLAP, plateau
2026-06-01 docs(stems): final perf table + TensorRT setup notes
2026-06-01 start-dj.sh: pick cue device adaptively (USB DAC → bluez → none)
    User booted with Bluetooth headphones today, no USB DAC plugged in.
    The hardcoded --cue-device "KT USB Audio" then fails cpal lookup
    and the binary exits with no cue.
    Discovery order now:
    1. $DJ_CUE_DEVICE override (manual escape hatch).
    2. UGREEN / KT USB Audio sink if it's around.
2026-06-01 docs(readme): setup section + commit the ONNX export scripts
    The README didn't mention stems, downbeat detection, or the ONNX
    model paths at all — anyone landing on the repo from a fresh clone
    had no obvious way to reproduce those features. Fix:
    - Feature list now calls out beat_this downbeat detection and live
    HTDemucs stem separation (with the recent ~7 s/track number).
    - New "Setup" section in the README spells out:
